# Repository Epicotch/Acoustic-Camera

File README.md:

hi

Firmware is under firmware, actual board is under Microphone board (KiCAD 10), analysis tools is are in pattern analysis, power viewing utility is under power viewer

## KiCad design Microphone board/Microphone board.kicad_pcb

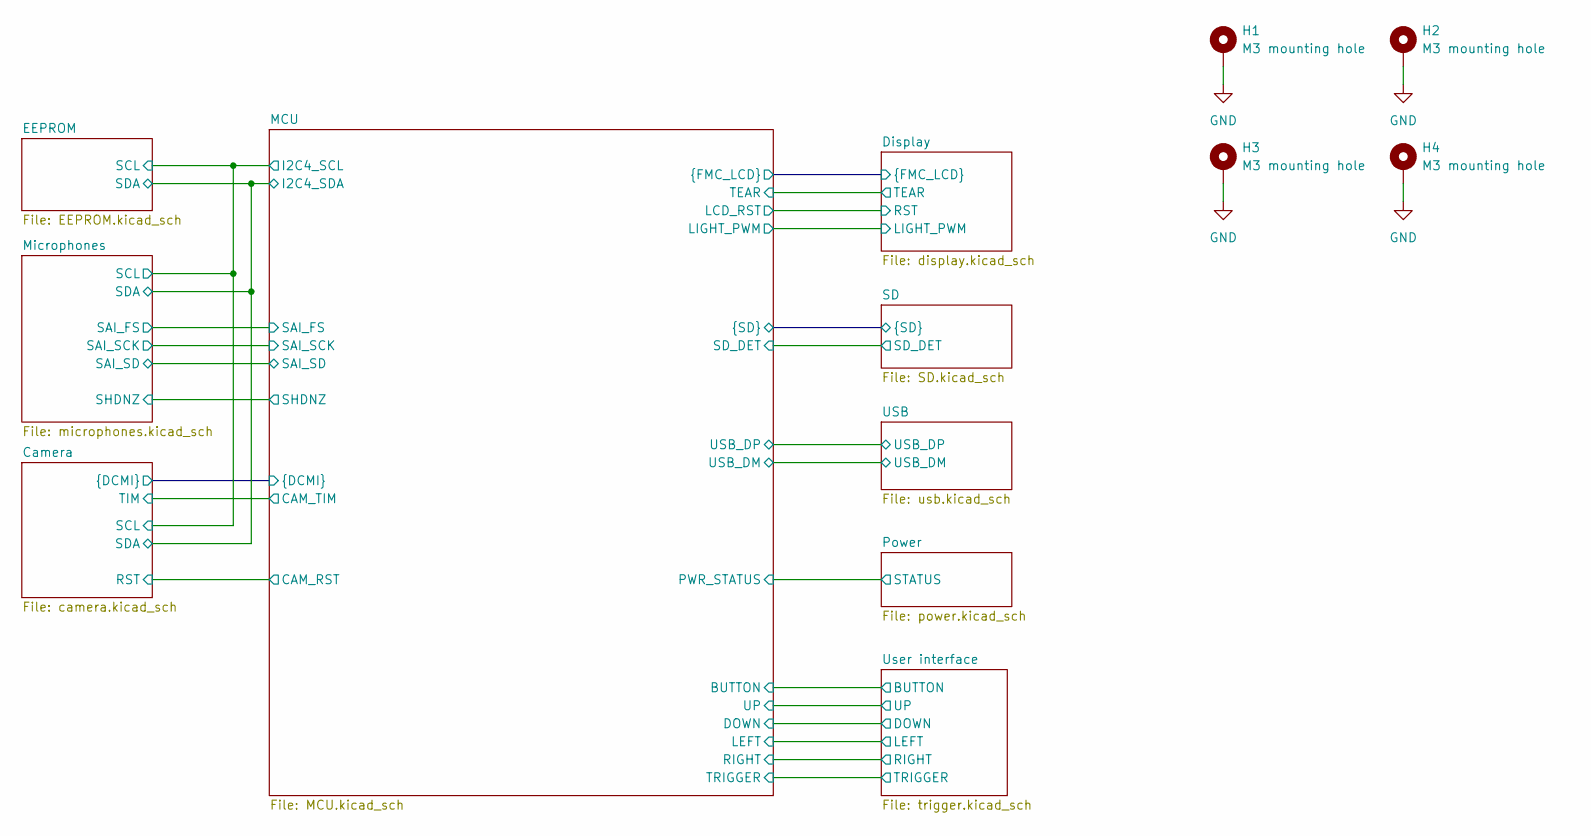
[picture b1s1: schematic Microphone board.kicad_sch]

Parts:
H1, H2, H3, H4: M3 mounting hole; MountingHole_3.2mm_M3_DIN965_Pad

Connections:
GND: H1.1 (1_1), H2.1 (1_1), H3.1 (1_1), H4.1 (1_1); also elsewhere on the board

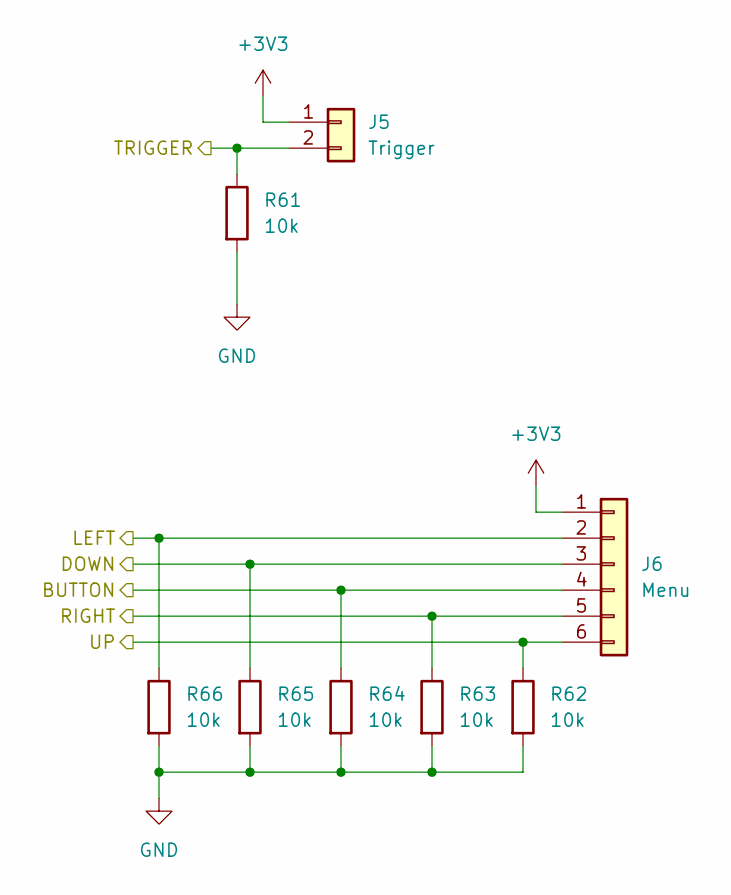
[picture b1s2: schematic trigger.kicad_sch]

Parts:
J5: Trigger; JST_PH_B2B-PH-K_1x02_P2.00mm_Vertical
J6: Menu; JST_PH_B6B-PH-K_1x06_P2.00mm_Vertical
R61, R62, R63, R64, R65, R66: 10k; R_0402_1005Metric

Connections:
+3V3: J5.1, J6.1; also elsewhere on the board
/MCU/BUTTON: J6.4, R64.1; also elsewhere on the board
/MCU/DOWN: J6.3, R65.1; also elsewhere on the board
/MCU/LEFT: J6.2, R66.1; also elsewhere on the board
/MCU/RIGHT: J6.5, R63.1; also elsewhere on the board
/MCU/TRIGGER: J5.2, R61.1; also elsewhere on the board
/MCU/UP: J6.6, R62.1; also elsewhere on the board
GND: R61.2, R62.2, R63.2, R64.2, R65.2, R66.2; also elsewhere on the board

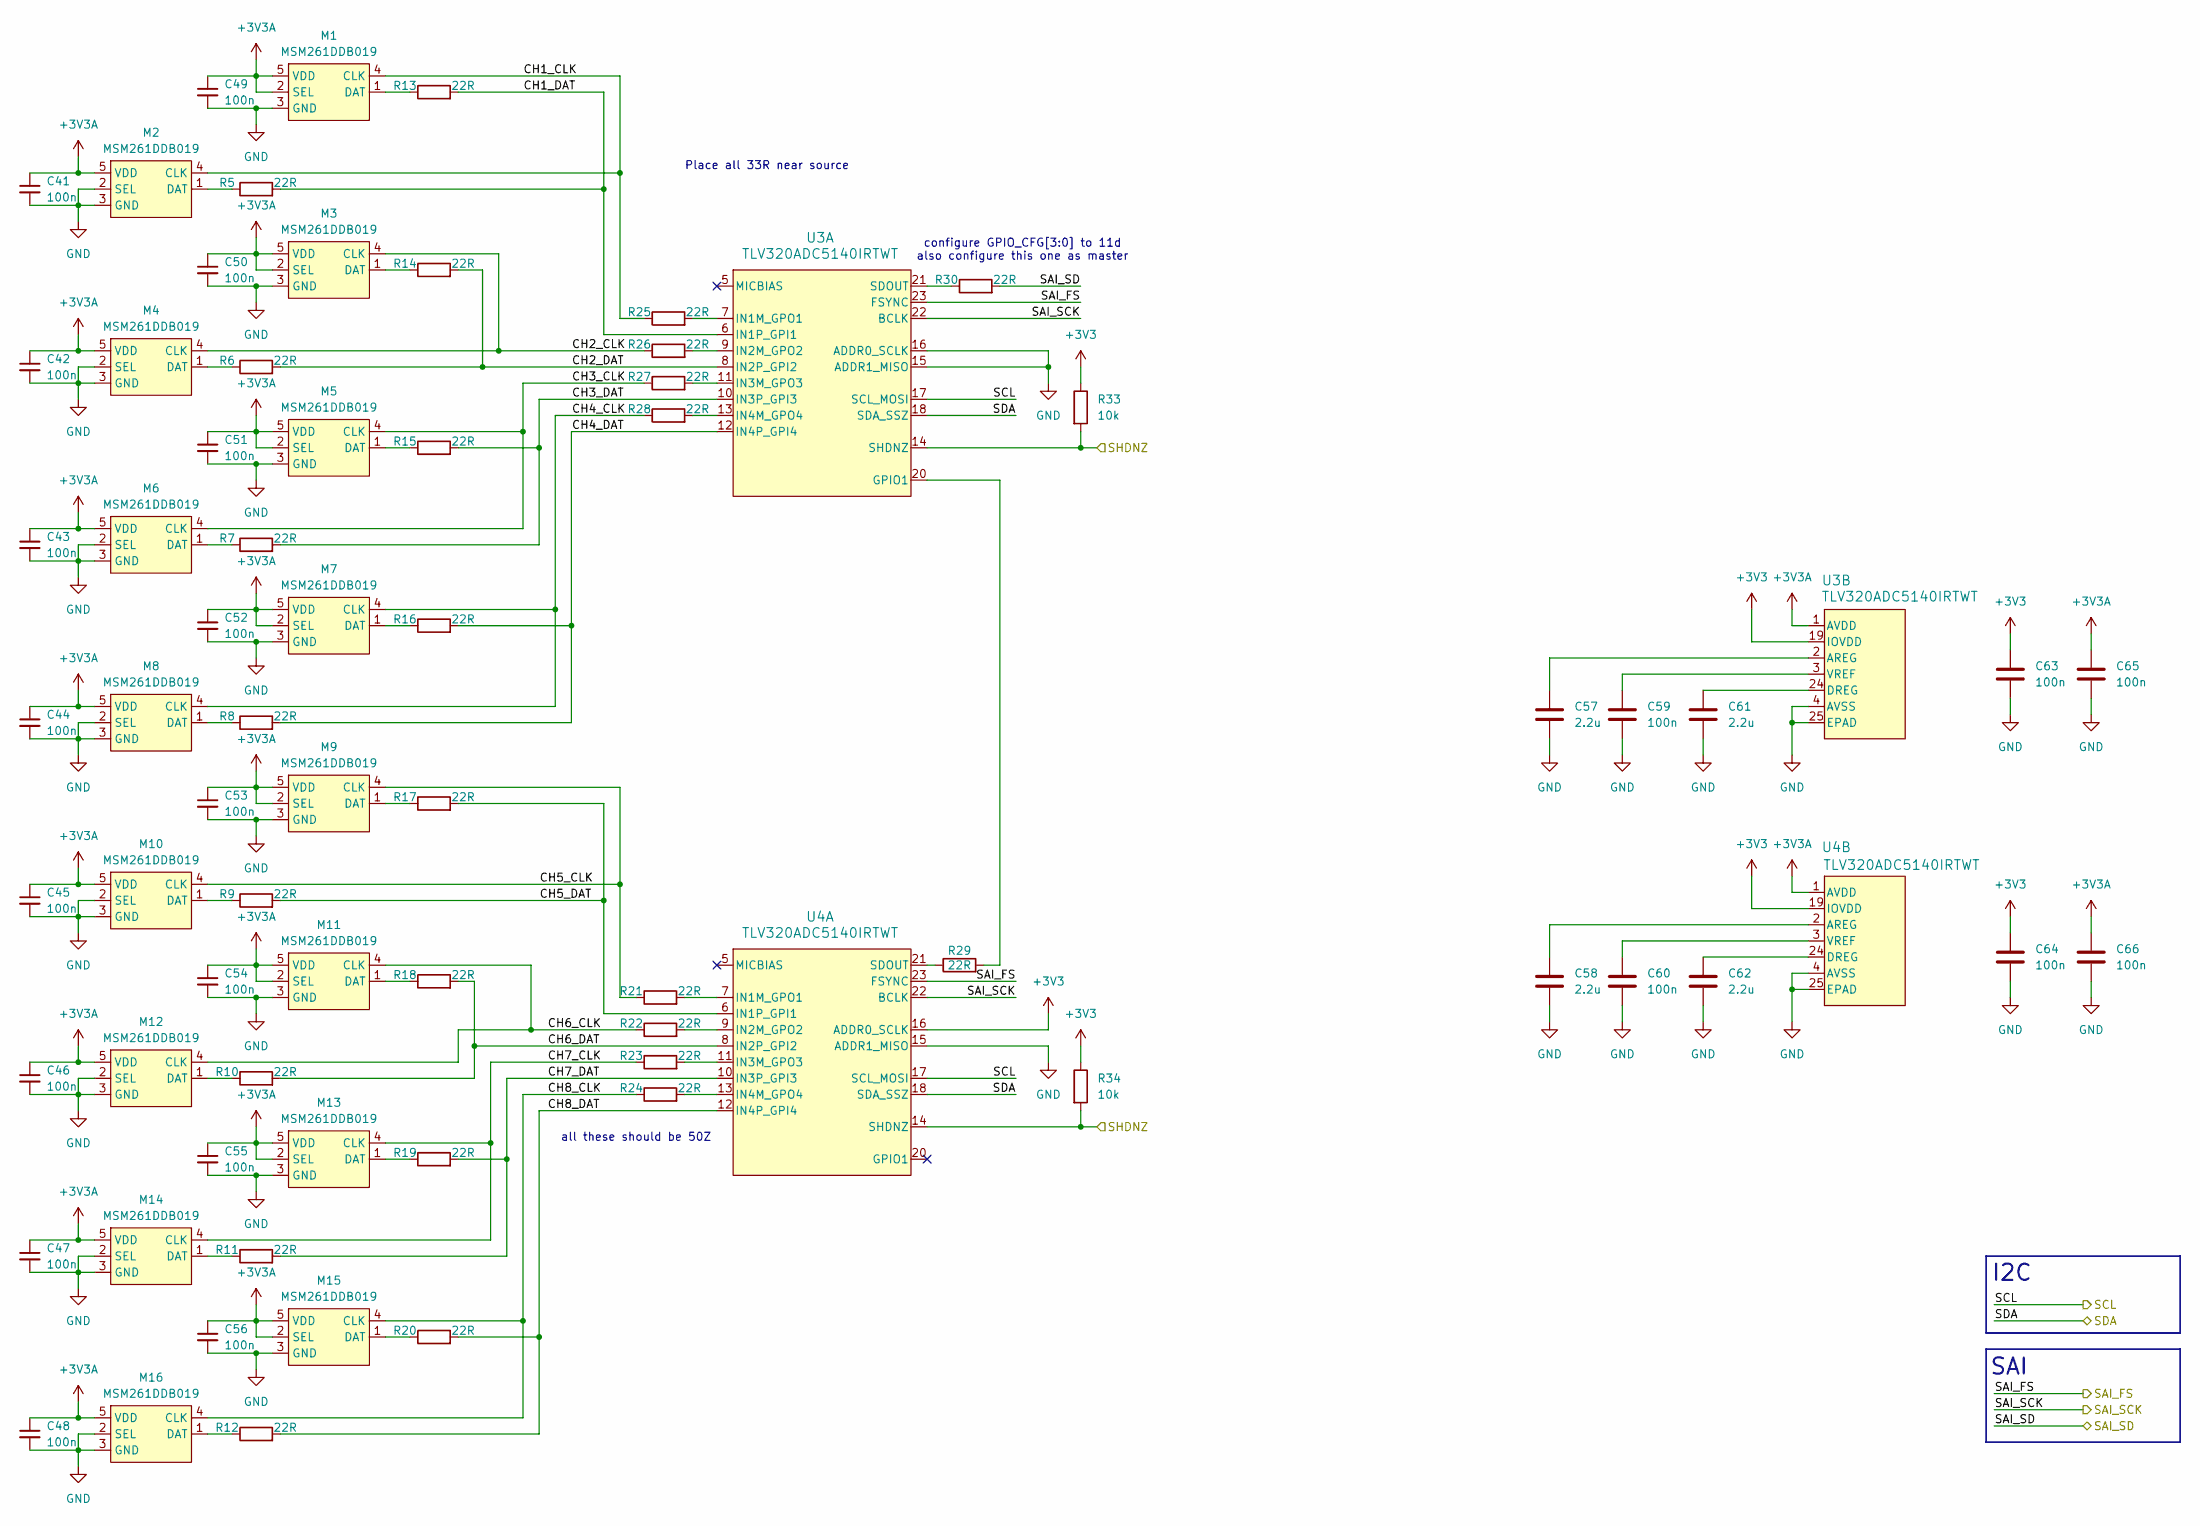
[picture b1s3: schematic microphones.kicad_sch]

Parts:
C41, C42, C43, C44, C45, C46, C47, C48, C49, C50, C51, C52, C53, C54, C55, C56, C59, C60, C63, C64, C65, C66: 100n; C_0402_1005Metric
C57, C58, C61, C62: 2.2u; C_0402_1005Metric
M1, M2, M3, M4, M5, M6, M7, M8, M9, M10, M11, M12, M13, M14, M15, M16: MSM261DDB019
R5, R6, R7, R8, R9, R10, R11, R12, R13, R14, R15, R16, R17, R18, R19, R20, R21, R22, R23, R24, R25, R26, R27, R28, R29, R30: 22R; R_0402_1005Metric
R33, R34: 10k; R_0402_1005Metric
U3, U4: TLV320ADC5140IRTWT; RTW24_4P15X4P15_TEX

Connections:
+3V3: C63.1, C64.1, R33.1, R34.1, U3.19 (IOVDD), U4.16 (ADDR0_SCLK), U4.19 (IOVDD); also elsewhere on the board
+3V3A: C41.1, C42.1, C43.1, C44.1, C45.1, C46.1, C47.1, C48.1, C49.1, C50.1, C51.1, C52.1, C53.1, C54.1, C55.1, C56.1, C65.1, C66.1, M1.2 (SEL), M1.5 (VDD), M2.5 (VDD), M3.2 (SEL), M3.5 (VDD), M4.5 (VDD), M5.2 (SEL), M5.5 (VDD), M6.5 (VDD), M7.2 (SEL), M7.5 (VDD), M8.5 (VDD), M9.2 (SEL), M9.5 (VDD), M10.5 (VDD), M11.2 (SEL), M11.5 (VDD), M12.5 (VDD), M13.2 (SEL), M13.5 (VDD), M14.5 (VDD), M15.2 (SEL), M15.5 (VDD), M16.5 (VDD), U3.1 (AVDD), U4.1 (AVDD); also elsewhere on the board
/MCU/I2C4_SCL: U3.17 (SCL_MOSI), U4.17 (SCL_MOSI); also elsewhere on the board
/MCU/I2C4_SDA: U3.18 (SDA_SSZ), U4.18 (SDA_SSZ); also elsewhere on the board
/MCU/SAI_FS: U3.23 (FSYNC), U4.23 (FSYNC); also elsewhere on the board
/MCU/SAI_SCK: U3.22 (BCLK), U4.22 (BCLK); also elsewhere on the board
/MCU/SAI_SD: R30.2; also elsewhere on the board
/MCU/SHDNZ: R33.2, R34.2, U3.14 (SHDNZ), U4.14 (SHDNZ); also elsewhere on the board
/Microphones/CH1_CLK: M1.4 (CLK), M2.4 (CLK), R25.1
/Microphones/CH1_DAT: R5.2, R13.2, U3.6 (IN1P_GPI1)
/Microphones/CH2_CLK: M3.4 (CLK), M4.4 (CLK), R26.1
/Microphones/CH2_DAT: R6.2, R14.2, U3.8 (IN2P_GPI2)
/Microphones/CH3_CLK: M5.4 (CLK), M6.4 (CLK), R27.1
/Microphones/CH3_DAT: R7.2, R15.2, U3.10 (IN3P_GPI3)
/Microphones/CH4_CLK: M7.4 (CLK), M8.4 (CLK), R28.1
/Microphones/CH4_DAT: R8.2, R16.2, U3.12 (IN4P_GPI4)
/Microphones/CH5_CLK: M9.4 (CLK), M10.4 (CLK), R21.1
/Microphones/CH5_DAT: R9.2, R17.2, U4.6 (IN1P_GPI1)
/Microphones/CH6_CLK: M11.4 (CLK), M12.4 (CLK), R22.1
/Microphones/CH6_DAT: R10.2, R18.2, U4.8 (IN2P_GPI2)
/Microphones/CH7_CLK: M13.4 (CLK), M14.4 (CLK), R23.1
/Microphones/CH7_DAT: R11.2, R19.2, U4.10 (IN3P_GPI3)
/Microphones/CH8_CLK: M15.4 (CLK), M16.4 (CLK), R24.1
/Microphones/CH8_DAT: R12.2, R20.2, U4.12 (IN4P_GPI4)
GND: C41.2, C42.2, C43.2, C44.2, C45.2, C46.2, C47.2, C48.2, C49.2, C50.2, C51.2, C52.2, C53.2, C54.2, C55.2, C56.2, C57.2, C58.2, C59.2, C60.2, C61.2, C62.2, C63.2, C64.2, C65.2, C66.2, M1.3 (GND), M2.2 (SEL), M2.3 (GND), M3.3 (GND), M4.2 (SEL), M4.3 (GND), M5.3 (GND), M6.2 (SEL), M6.3 (GND), M7.3 (GND), M8.2 (SEL), M8.3 (GND), M9.3 (GND), M10.2 (SEL), M10.3 (GND), M11.3 (GND), M12.2 (SEL), M12.3 (GND), M13.3 (GND), M14.2 (SEL), M14.3 (GND), M15.3 (GND), M16.2 (SEL), M16.3 (GND), U3.4 (AVSS), U3.15 (ADDR1_MISO), U3.16 (ADDR0_SCLK), U3.25 (EPAD), U4.4 (AVSS), U4.15 (ADDR1_MISO), U4.25 (EPAD); also elsewhere on the board
unnamed: M1.1 (DAT), R13.1
unnamed: M2.1 (DAT), R5.1
unnamed: M3.1 (DAT), R14.1
unnamed: M4.1 (DAT), R6.1
unnamed: M5.1 (DAT), R15.1
unnamed: M6.1 (DAT), R7.1
unnamed: M7.1 (DAT), R16.1
unnamed: M8.1 (DAT), R8.1
unnamed: M9.1 (DAT), R17.1
unnamed: M10.1 (DAT), R9.1
unnamed: M11.1 (DAT), R18.1
unnamed: M12.1 (DAT), R10.1
unnamed: M13.1 (DAT), R19.1
unnamed: M14.1 (DAT), R11.1
unnamed: M15.1 (DAT), R20.1
unnamed: M16.1 (DAT), R12.1
unnamed: R29.2, U3.20 (GPIO1)
unnamed: R25.2, U3.7 (IN1M_GPO1)
unnamed: R26.2, U3.9 (IN2M_GPO2)
unnamed: R27.2, U3.11 (IN3M_GPO3)
unnamed: R28.2, U3.13 (IN4M_GPO4)
unnamed: R30.1, U3.21 (SDOUT)
unnamed: C57.1, U3.2 (AREG)
unnamed: C61.1, U3.24 (DREG)
unnamed: C59.1, U3.3 (VREF)
unnamed: R21.2, U4.7 (IN1M_GPO1)
unnamed: R22.2, U4.9 (IN2M_GPO2)
unnamed: R23.2, U4.11 (IN3M_GPO3)
unnamed: R24.2, U4.13 (IN4M_GPO4)
unnamed: R29.1, U4.21 (SDOUT)
unnamed: C58.1, U4.2 (AREG)
unnamed: C62.1, U4.24 (DREG)
unnamed: C60.1, U4.3 (VREF)

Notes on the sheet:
SAI
Place all 33R near source
configure GPIO_CFG[3:0] to 11d also configure this one as master
I2C
all these should be 50Z

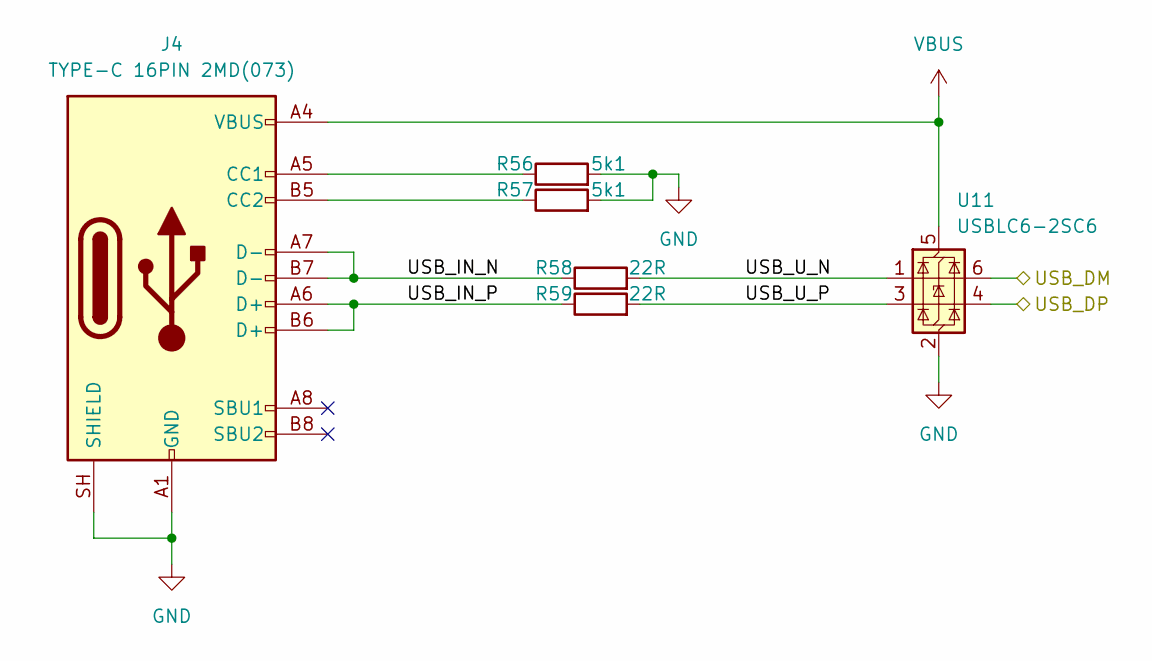
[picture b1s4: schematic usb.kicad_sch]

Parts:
J4: TYPE-C 16PIN 2MD(073); USB_C_Receptacle_HRO_TYPE-C-31-M-12
R56, R57: 5k1; R_0402_1005Metric
R58, R59: 22R; R_0402_1005Metric
U11: USBLC6-2SC6; SOT-23-6

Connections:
/MCU/USB_N: U11.6 (I/O1); also elsewhere on the board
/MCU/USB_P: U11.4 (I/O2); also elsewhere on the board
/USB/USB_IN_N: J4.A7 (D-), J4.B7 (D-), R58.1
/USB/USB_IN_P: J4.A6 (D+), J4.B6 (D+), R59.1
/USB/USB_U_N: R58.2, U11.1 (I/O1)
/USB/USB_U_P: R59.2, U11.3 (I/O2)
GND: J4.A1 (GND), J4.A12 (GND), J4.B1 (GND), J4.B12 (GND), J4.SH (SHIELD), R56.2, R57.2, U11.2 (GND); also elsewhere on the board
unnamed: J4.A5 (CC1), R56.1
unnamed: J4.B5 (CC2), R57.1
VBUS: J4.A4 (VBUS), J4.A9 (VBUS), J4.B4 (VBUS), J4.B9 (VBUS), U11.5 (VBUS); also elsewhere on the board

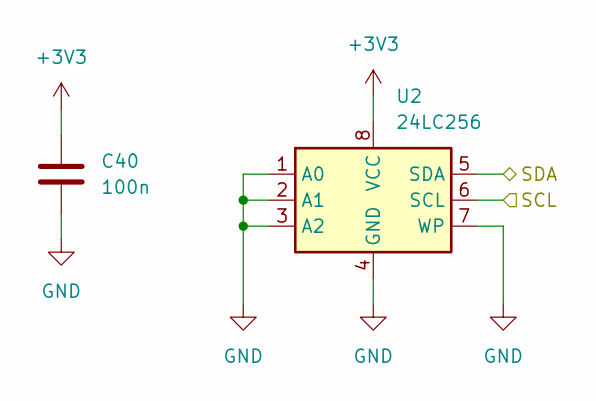
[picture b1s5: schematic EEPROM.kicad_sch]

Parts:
C40: 100n; C_0402_1005Metric
U2: 24LC256; SOIC-8_3.9x4.9mm_P1.27mm

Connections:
+3V3: C40.1, U2.8 (VCC); also elsewhere on the board
/MCU/I2C4_SCL: U2.6 (SCL); also elsewhere on the board
/MCU/I2C4_SDA: U2.5 (SDA); also elsewhere on the board
GND: C40.2, U2.1 (A0), U2.2 (A1), U2.3 (A2), U2.4 (GND), U2.7 (WP); also elsewhere on the board

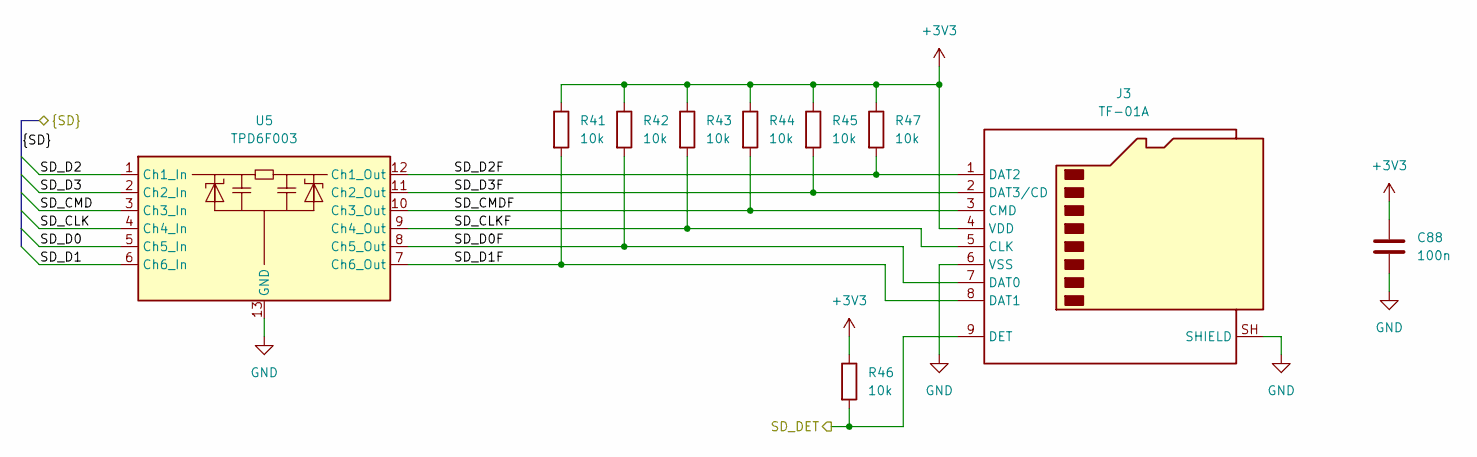
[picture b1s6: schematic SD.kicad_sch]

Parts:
C88: 100n; C_0402_1005Metric
J3: TF-01A
R41, R42, R43, R44, R45, R46, R47: 10k; R_0402_1005Metric
U5: TPD6F003; Texas_R-PWSON-N12_EP0.4x2mm

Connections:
+3V3: C88.1, J3.4 (VDD), R41.1, R42.1, R43.1, R44.1, R45.1, R46.1, R47.1; also elsewhere on the board
/MCU/SD_CLK: U5.4 (Ch4_In); also elsewhere on the board
/MCU/SD_CMD: U5.3 (Ch3_In); also elsewhere on the board
/MCU/SD_D0: U5.5 (Ch5_In); also elsewhere on the board
/MCU/SD_D1: U5.6 (Ch6_In); also elsewhere on the board
/MCU/SD_D2: U5.1 (Ch1_In); also elsewhere on the board
/MCU/SD_D3: U5.2 (Ch2_In); also elsewhere on the board
/MCU/SD_DET: J3.9 (DET), R46.2; also elsewhere on the board
/SD/SD_CLKF: J3.5 (CLK), R43.2, U5.9 (Ch4_Out)
/SD/SD_CMDF: J3.3 (CMD), R44.2, U5.10 (Ch3_Out)
/SD/SD_D0F: J3.7 (DAT0), R42.2, U5.8 (Ch5_Out)
/SD/SD_D1F: J3.8 (DAT1), R41.2, U5.7 (Ch6_Out)
/SD/SD_D2F: J3.1 (DAT2), R47.2, U5.12 (Ch1_Out)
/SD/SD_D3F: J3.2 (DAT3/CD), R45.2, U5.11 (Ch2_Out)
GND: C88.2, J3.6 (VSS), J3.SH (SHIELD), U5.13 (GND); also elsewhere on the board

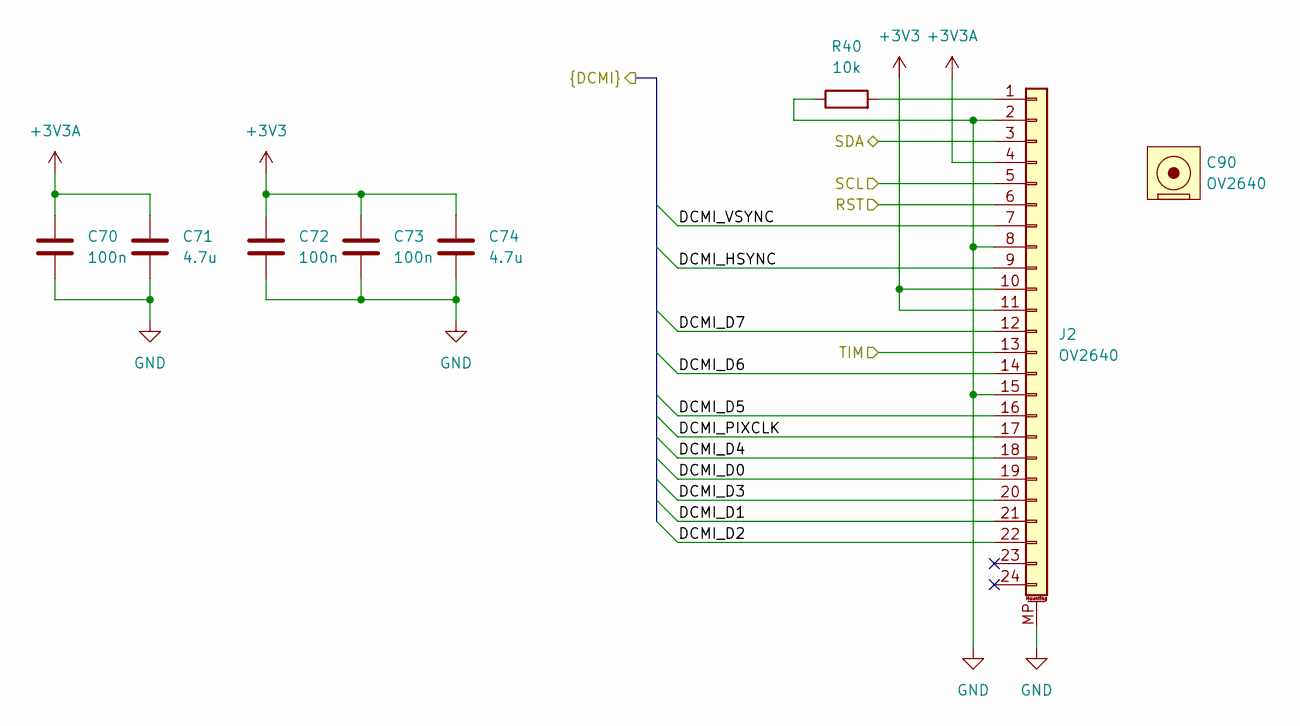
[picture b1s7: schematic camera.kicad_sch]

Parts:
C70, C72, C73: 100n; C_0402_1005Metric
C71, C74: 4.7u; C_0603_1608Metric
C90: OV2640
J2: OV2640; Hirose_FH12-24S-0.5SH_1x24-1MP_P0.50mm_Horizontal
R40: 10k; R_0402_1005Metric

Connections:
+3V3: C72.1, C73.1, C74.1, J2.10, J2.11; also elsewhere on the board
+3V3A: C70.1, C71.1, J2.4; also elsewhere on the board
/MCU/CAM_RST: J2.6; also elsewhere on the board
/MCU/CAM_TIM: J2.13; also elsewhere on the board
/MCU/DCMI_D0: J2.19; also elsewhere on the board
/MCU/DCMI_D1: J2.21; also elsewhere on the board
/MCU/DCMI_D2: J2.22; also elsewhere on the board
/MCU/DCMI_D3: J2.20; also elsewhere on the board
/MCU/DCMI_D4: J2.18; also elsewhere on the board
/MCU/DCMI_D5: J2.16; also elsewhere on the board
/MCU/DCMI_D6: J2.14; also elsewhere on the board
/MCU/DCMI_D7: J2.12; also elsewhere on the board
/MCU/DCMI_HSYNC: J2.9; also elsewhere on the board
/MCU/DCMI_PIXCLK: J2.17; also elsewhere on the board
/MCU/DCMI_VSYNC: J2.7; also elsewhere on the board
/MCU/I2C4_SCL: J2.5; also elsewhere on the board
/MCU/I2C4_SDA: J2.3; also elsewhere on the board
GND: C70.2, C71.2, C72.2, C73.2, C74.2, J2.2, J2.8, J2.15, J2.MP (MountPin), R40.1; also elsewhere on the board
unnamed: J2.1, R40.2

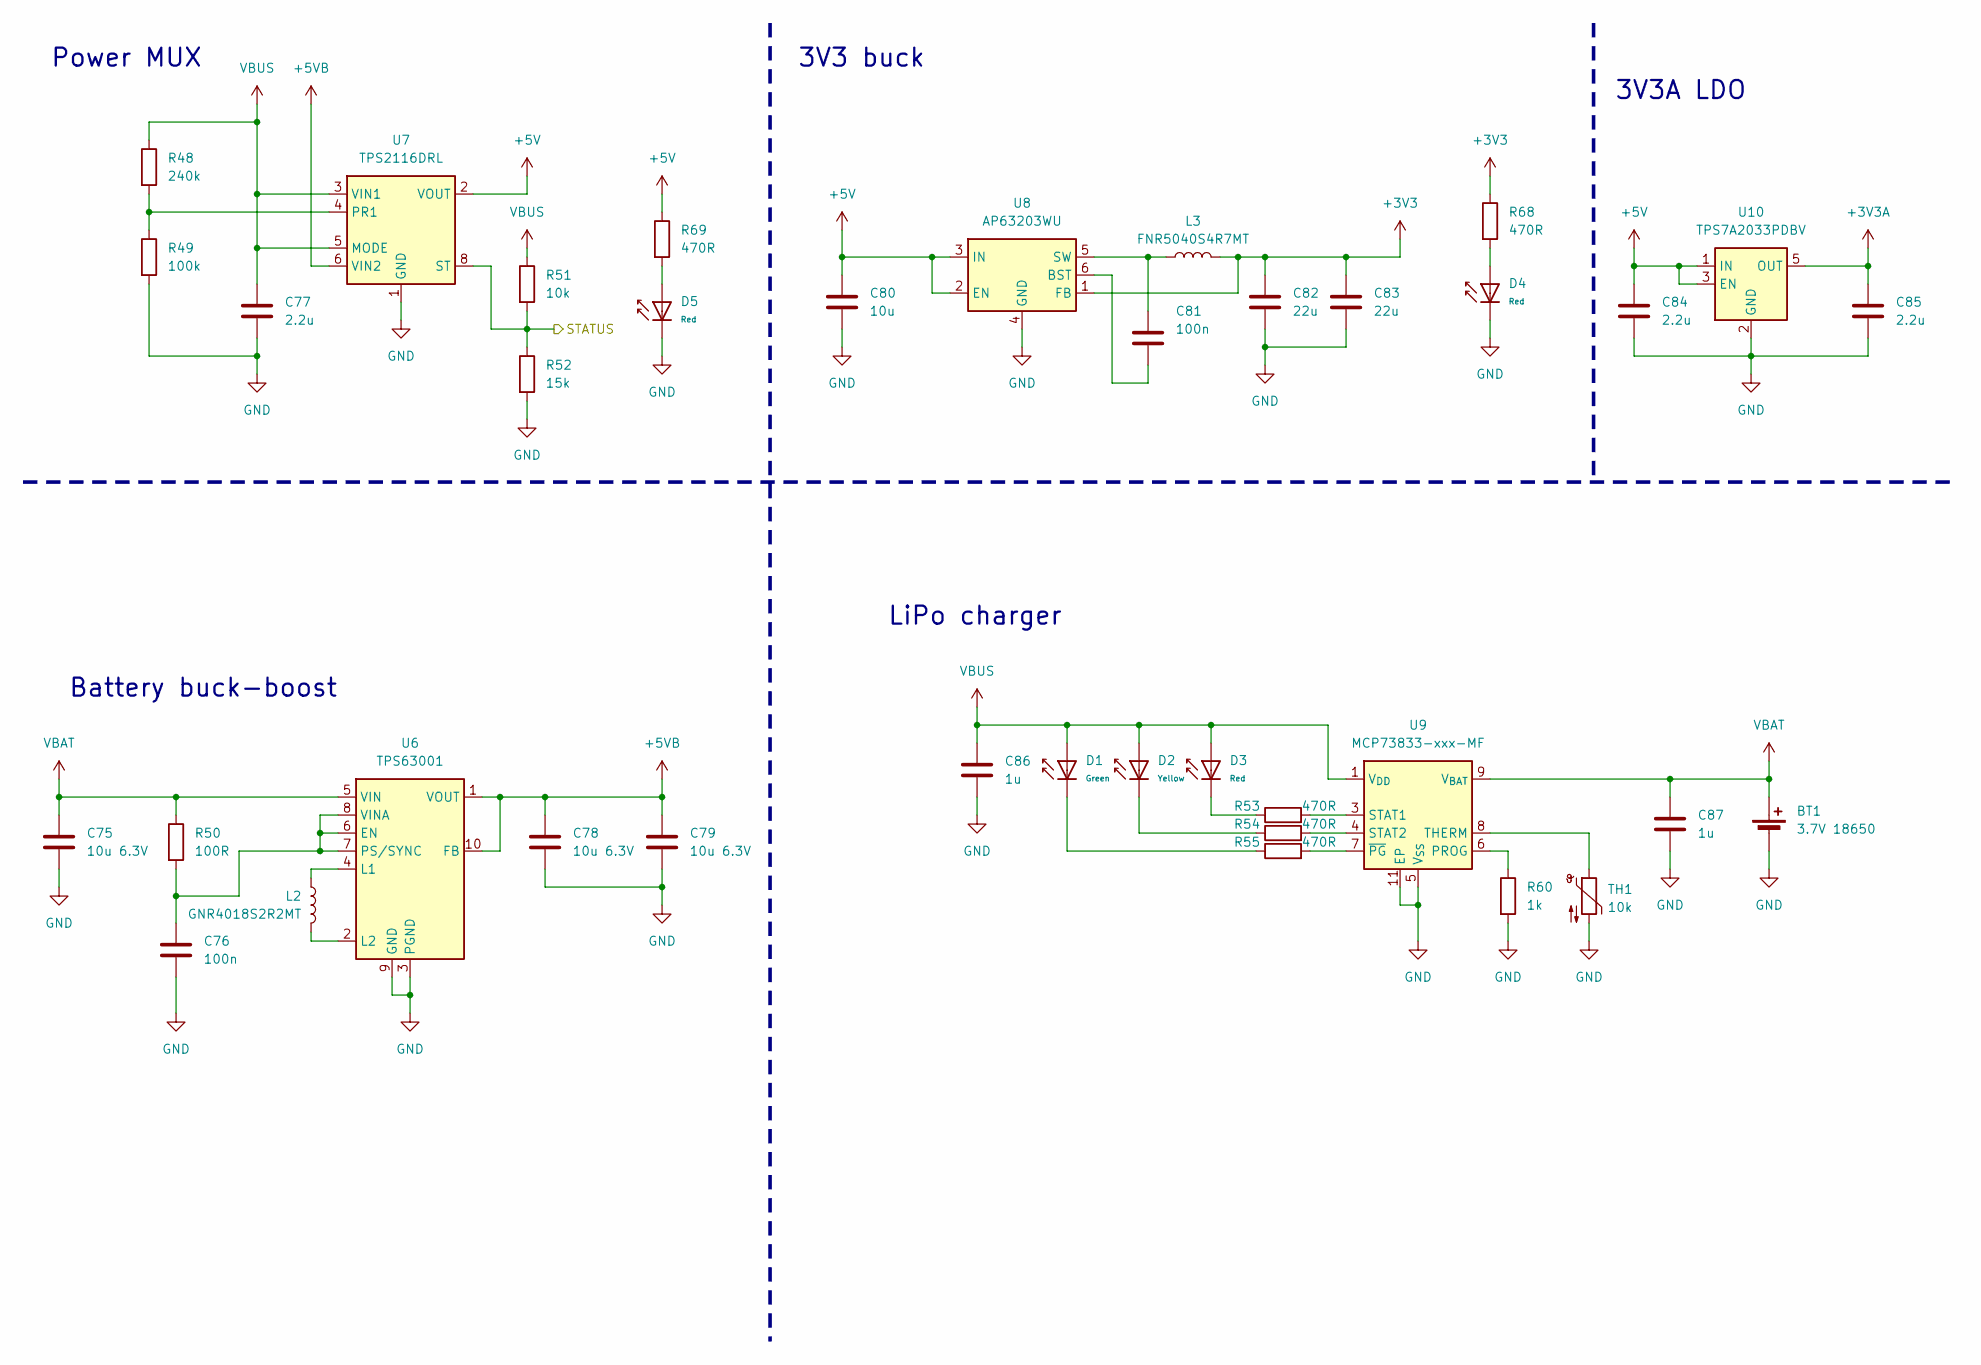
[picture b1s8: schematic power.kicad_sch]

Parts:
BT1: 3.7V 18650; SolderWire-1.5sqmm_1x02_P6mm_D1.7mm_OD3mm
C75, C78, C79: 10u 6.3V; C_0805_2012Metric
C76, C81: 100n; C_0402_1005Metric
C77: 2.2u; C_0402_1005Metric
C80: 10u; C_0603_1608Metric
C82, C83: 22u; C_0805_2012Metric
C84, C85: 2.2u; C_0603_1608Metric
C86, C87: 1u; C_0603_1608Metric
D1: Green; D_0603; Forward Voltage (VF) 1.6V~2.6V; Part NCD0603Y2; LCSC C89811
D2: Yellow; D_0603; Forward Voltage (VF) 1.6V~2.6V; Part NCD0603Y2; LCSC C89811
D3, D4, D5: Red; D_0603; Part KT-0603R; LCSC C2286
L2: GNR4018S2R2MT; L_Abracon_ASPI-4030S
L3: FNR5040S4R7MT; L_Changjiang_FNR5040S
R48: 240k; R_0402_1005Metric
R49: 100k; R_0402_1005Metric
R50: 100R; R_0402_1005Metric
R51: 10k; R_0402_1005Metric
R52: 15k; R_0402_1005Metric
R53, R54, R55, R68, R69: 470R; R_0402_1005Metric
R60: 1k; R_0402_1005Metric
TH1: 10k; JST_PH_B2B-PH-K_1x02_P2.00mm_Vertical
U6: TPS63001; Texas_DRC0010J_ThermalVias
U7: TPS2116DRL; SOT-583-8
U8: AP63203WU; TSOT-23-6
U9: MCP73833-xxx-MF; DFN-10-1EP_3x3mm_P0.5mm_EP1.58x2.35mm
U10: TPS7A2033PDBV; SOT-23-5

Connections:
+3V3: C82.1, C83.1, L3.2, R68.1, U8.1 (FB); also elsewhere on the board
+3V3A: C85.1, U10.5 (OUT); also elsewhere on the board
+5V: C80.1, C84.1, R69.1, U7.2 (VOUT), U7.7 (VOUT), U8.2 (EN), U8.3 (IN), U10.1 (IN), U10.3 (EN)
+5VB: C78.1, C79.1, U6.1 (VOUT), U6.10 (FB), U7.6 (VIN2)
/MCU/PWR_STATUS: R51.2, R52.1, U7.8 (ST); also elsewhere on the board
GND: BT1.2 (-), C75.2, C76.2, C77.2, C78.2, C79.2, C80.2, C82.2, C83.2, C84.2, C85.2, C86.2, C87.2, D4.1, D5.1, R49.2, R52.2, R60.2, TH1.2, U6.3 (PGND), U6.9 (GND), U6.11 (PGND), U7.1 (GND), U8.4 (GND), U9.5 (V_{SS}), U9.11 (EP), U10.2 (GND); also elsewhere on the board
unnamed: D1.1, R55.1
unnamed: D2.1, R54.1
unnamed: D3.1, R53.1
unnamed: D4.2, R68.2
unnamed: D5.2, R69.2
unnamed: C76.1, R50.2, U6.6 (EN), U6.7 (PS/SYNC), U6.8 (VINA)
unnamed: L2.2, U6.4 (L1)
unnamed: L2.1, U6.2 (L2)
unnamed: R48.2, R49.1, U7.4 (PR1)
unnamed: C81.2, U8.6 (BST)
unnamed: C81.1, L3.1, U8.5 (SW)
unnamed: R60.1, U9.6 (PROG)
unnamed: R53.2, U9.3 (STAT1)
unnamed: R54.2, U9.4 (STAT2)
unnamed: TH1.1, U9.8 (THERM)
unnamed: R55.2, U9.7 (~PG)
VBAT: BT1.1 (+), C75.1, C87.1, R50.1, U6.5 (VIN), U9.9 (V_{BAT}), U9.10 (V_{BAT})
VBUS: C77.1, C86.1, D1.2, D2.2, D3.2, R48.1, R51.1, U7.3 (VIN1), U7.5 (MODE), U9.1 (V_{DD}), U9.2 (V_{DD}); also elsewhere on the board

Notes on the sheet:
3V3 buck
3V3A LDO
LiPo charger
Battery buck-boost
Power MUX

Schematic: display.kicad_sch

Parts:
C67, C68: 100n; C_0402_1005Metric
C69: 4.7u; C_0603_1608Metric
J1: NHD-2.4-240320AF-CSXP; Hirose_FH12-40S-0.5SH_1x40-1MP_P0.50mm_Horizontal
Q1: MMBT3904; SOT-23
Q2: AO3401A; SOT-23
R35: 1k; R_0402_1005Metric
R36: 10k; R_0402_1005Metric
R37: 4k7; R_0402_1005Metric
R38: 10R; R_0402_1005Metric
R39: 2R; R_0603_1608Metric

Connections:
+3V3: C67.1, C68.1, C69.1, J1.33, J1.34, Q2.2 (S), R37.2; also elsewhere on the board
/Display/LIGHT: J1.3, R39.2
/MCU/FMC_D0: J1.27; also elsewhere on the board
/MCU/FMC_D1: J1.26; also elsewhere on the board
/MCU/FMC_D2: J1.25; also elsewhere on the board
/MCU/FMC_D3: J1.24; also elsewhere on the board
/MCU/FMC_D4: J1.23; also elsewhere on the board
/MCU/FMC_D5: J1.22; also elsewhere on the board
/MCU/FMC_D6: J1.21; also elsewhere on the board
/MCU/FMC_D7: J1.20; also elsewhere on the board
/MCU/FMC_D8: J1.19; also elsewhere on the board
/MCU/FMC_D9: J1.18; also elsewhere on the board
/MCU/FMC_D10: J1.17; also elsewhere on the board
/MCU/FMC_D11: J1.16; also elsewhere on the board
/MCU/FMC_D12: J1.15; also elsewhere on the board
/MCU/FMC_D13: J1.14; also elsewhere on the board
/MCU/FMC_D14: J1.13; also elsewhere on the board
/MCU/FMC_D15: J1.12; also elsewhere on the board
/MCU/FMC_NE1: J1.31; also elsewhere on the board
/MCU/FMC_NOE: J1.28; also elsewhere on the board
/MCU/FMC_NWE: J1.29; also elsewhere on the board
/MCU/FMC_RS: J1.30; also elsewhere on the board
/MCU/LCD_RST: J1.11; also elsewhere on the board
/MCU/LIGHT_PWM: R35.1; also elsewhere on the board
/MCU/TEAR: J1.1; also elsewhere on the board
GND: C67.2, C68.2, C69.2, J1.2, J1.4, J1.5, J1.6, J1.7, J1.8, J1.9, J1.10, J1.32, J1.40, J1.MP (MountPin), Q1.2 (E), R36.1; also elsewhere on the board
unnamed: Q1.1 (B), R35.2, R36.2
unnamed: Q1.3 (C), R37.1, R38.1
unnamed: Q2.3 (D), R39.1
unnamed: Q2.1 (G), R38.2

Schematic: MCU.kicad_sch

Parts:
C1: 220pF; C_0402_1005Metric
C2, C3, C5: 2.2u; C_0603_1608Metric
C4, C37: 4.7u; C_0603_1608Metric
C6, C7: 10u; C_0805_2012Metric
C8, C9, C10, C11, C12, C13, C14, C16, C17, C18, C19, C20, C21, C22, C23, C24, C25, C26, C27, C28, C29, C30, C31, C32, C33, C34, C35, C36, C89: 100n; C_0201_0603Metric
C15, C38: 1u; C_0603_1608Metric
C39: 100n; C_0402_1005Metric
D6: Red; D_0603; Part KT-0603R; LCSC C2286
J7: Conn_ARM_JTAG_SWD_10; PinHeader_2x05_P1.27mm_Vertical_SMD
L1: GNR4018S2R2MT; L_Abracon_ASPI-4030S
R1, R4: 10k; R_0402_1005Metric
R2, R3: 2k2; R_0402_1005Metric
R67: 22R; R_0402_1005Metric
R70: 470R; R_0402_1005Metric
S1, S2: Tactile Button, 160gf; SW_TS-1088-AR02016; Voltage Rating (Dc) 12V; Part TS-1088-AR02016; LCSC C720477
U1: STM32H747XIH6; TFBGA-265_14x14mm_Layout17x17_P0.8mm
Y1: SX2M25.000M20F30TNN; Oscillator_SMD_Kyocera_KC2520Z-4Pin_2.5x2.0mm

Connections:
+3V3: C6.1, C7.1, C8.1, C9.1, C10.1, C12.1, C13.1, C14.1, C16.1, C17.1, C18.1, C19.1, C20.1, C21.1, C22.1, C23.1, C24.1, C25.1, C26.1, C27.1, C28.1, C29.1, C30.1, C31.1, C32.1, C33.1, C34.1, C35.1, C36.1, C37.1, C38.1, C39.1, C89.1, J7.1 (VTref), L1.2, R1.1, R2.1, R3.1, S2.1 (A), U1.A6 (VDDLDO), U1.B1 (VBAT), U1.C17 (VDDLDO), U1.E6 (VDD), U1.E7 (PDR_ON), U1.E9 (VDD), U1.E11 (VDD), U1.F5 (VDD), U1.F17 (VDD33_USB), U1.G2 (VFBSMPS), U1.G5 (VDD), U1.G13 (VDD), U1.G17 (VDD50_USB), U1.H5 (VDD), U1.H13 (VDD), U1.J13 (VDD), U1.K5 (VDD), U1.K13 (VDD), U1.L5 (VDD), U1.L13 (VDD), U1.M5 (VDD), U1.M13 (VDD), U1.N7 (VDD), U1.N8 (VDD), U1.N10 (VDD), U1.N11 (VDD), U1.N12 (VDD), U1.P17 (VDDDSI), U1.U12 (VDDLDO), Y1.4 (VDD); also elsewhere on the board
+3V3A: C11.1, C15.1, U1.L1 (VDDA), U1.M1 (VREF+); also elsewhere on the board
/MCU/BOOT0: R4.1, S2.2 (B), U1.E8 (BOOT0)
/MCU/BUTTON: U1.U5 (PB0); also elsewhere on the board
/MCU/CAM_RST: U1.B5 (PB6); also elsewhere on the board
/MCU/CAM_TIM: R67.1; also elsewhere on the board
/MCU/DCMI_D0: U1.D15 (PA9); also elsewhere on the board
/MCU/DCMI_D1: U1.D14 (PA10); also elsewhere on the board
/MCU/DCMI_D2: U1.C4 (PE0); also elsewhere on the board
/MCU/DCMI_D3: U1.B4 (PE1); also elsewhere on the board
/MCU/DCMI_D4: U1.B17 (PH14); also elsewhere on the board
/MCU/DCMI_D5: U1.A4 (PI4); also elsewhere on the board
/MCU/DCMI_D6: U1.A2 (PI6); also elsewhere on the board
/MCU/DCMI_D7: U1.B3 (PI7); also elsewhere on the board
/MCU/DCMI_HSYNC: U1.T13 (PH8); also elsewhere on the board
/MCU/DCMI_PIXCLK: U1.R3 (PA6); also elsewhere on the board
/MCU/DCMI_VSYNC: U1.A3 (PI5); also elsewhere on the board
/MCU/DOWN: U1.U4 (PC5); also elsewhere on the board
/MCU/FMC_D0: U1.P16 (PD14); also elsewhere on the board
/MCU/FMC_D1: U1.P15 (PD15); also elsewhere on the board
/MCU/FMC_D2: U1.D13 (PD0); also elsewhere on the board
/MCU/FMC_D3: U1.E12 (PD1); also elsewhere on the board
/MCU/FMC_D4: U1.U9 (PE7); also elsewhere on the board
/MCU/FMC_D5: U1.T9 (PE8); also elsewhere on the board
/MCU/FMC_D6: U1.P9 (PE9); also elsewhere on the board
/MCU/FMC_D7: U1.N9 (PE10); also elsewhere on the board
/MCU/FMC_D8: U1.P10 (PE11); also elsewhere on the board
/MCU/FMC_D9: U1.R10 (PE12); also elsewhere on the board
/MCU/FMC_D10: U1.T10 (PE13); also elsewhere on the board
/MCU/FMC_D11: U1.U10 (PE14); also elsewhere on the board
/MCU/FMC_D12: U1.R11 (PE15); also elsewhere on the board
/MCU/FMC_D13: U1.U16 (PD8); also elsewhere on the board
/MCU/FMC_D14: U1.T17 (PD9); also elsewhere on the board
/MCU/FMC_D15: U1.T16 (PD10); also elsewhere on the board
/MCU/FMC_NE1: U1.C11 (PD7); also elsewhere on the board
/MCU/FMC_NOE: U1.A12 (PD4); also elsewhere on the board
/MCU/FMC_NWE: U1.A11 (PD5); also elsewhere on the board
/MCU/FMC_RS: U1.P7 (PF13); also elsewhere on the board
/MCU/HSE: U1.J2 (OSC_IN), Y1.3 (OUT)
/MCU/I2C4_SCL: R3.2, U1.P8 (PF14); also elsewhere on the board
/MCU/I2C4_SDA: R2.2, U1.R9 (PF15); also elsewhere on the board
/MCU/LCD_RST: U1.T15 (PB15); also elsewhere on the board
/MCU/LEFT: U1.U3 (PA4); also elsewhere on the board
/MCU/LIGHT_PWM: U1.P13 (PH10); also elsewhere on the board
/MCU/NRST: J7.10 (~RESET), R1.2, S1.1 (A), U1.K1 (NRST)
/MCU/PWR_STATUS: U1.H17 (PK2); also elsewhere on the board
/MCU/RIGHT: U1.U6 (PJ3); also elsewhere on the board
/MCU/SAI_FS: U1.D2 (PE4); also elsewhere on the board
/MCU/SAI_SCK: U1.D1 (PE5); also elsewhere on the board
/MCU/SAI_SD: U1.B11 (PD6); also elsewhere on the board
/MCU/SD_CLK: U1.C12; also elsewhere on the board
/MCU/SD_CMD: U1.D12 (PD2); also elsewhere on the board
/MCU/SD_D0: U1.E13 (PC8); also elsewhere on the board
/MCU/SD_D1: U1.E14 (PC9); also elsewhere on the board
/MCU/SD_D2: U1.A13 (PC10); also elsewhere on the board
/MCU/SD_D3: U1.B13 (PC11); also elsewhere on the board
/MCU/SD_DET: U1.A15 (PI1); also elsewhere on the board
/MCU/SHDNZ: U1.B10 (PJ15); also elsewhere on the board
/MCU/STATUS_LED: R70.1, U1.T3 (PA5)
/MCU/SWCLK: J7.4 (SWCLK/TCK), U1.B14 (SWCLK)
/MCU/SWDIO: J7.2 (SWDIO/TMS), U1.C15 (SWDIO)
/MCU/SWO: J7.6 (SWO/TDO), U1.R6 (PB2)
/MCU/TEAR: U1.U15 (PB14); also elsewhere on the board
/MCU/TRIGGER: U1.U2 (PA3); also elsewhere on the board
/MCU/UP: U1.U7 (PJ4); also elsewhere on the board
/MCU/USB_N: U1.E17 (PA11); also elsewhere on the board
/MCU/USB_P: U1.E16 (PA12); also elsewhere on the board
GND: C1.2, C2.2, C3.2, C4.2, C5.2, C6.2, C7.2, C8.2, C9.2, C10.2, C11.2, C12.2, C13.2, C14.2, C15.2, C16.2, C17.2, C18.2, C19.2, C20.2, C21.2, C22.2, C23.2, C24.2, C25.2, C26.2, C27.2, C28.2, C29.2, C30.2, C31.2, C32.2, C33.2, C34.2, C35.2, C36.2, C37.2, C38.2, C39.2, C89.2, D6.1, J7.3 (GND), J7.5 (GND), J7.9 (GNDDetect), R4.2, S1.2 (B), U1.A1 (VSS), U1.A17 (VSS), U1.B2 (VSS), U1.B6 (VSS), U1.C10 (VSS), U1.C13 (VSS), U1.C16 (VSS), U1.F2 (VSSSMPS), U1.G7 (VSS), U1.G8 (VSS), U1.G9 (VSS), U1.G10 (VSS), U1.G11 (VSS), U1.G16 (VSS), U1.H7 (VSS), U1.H8 (VSS), U1.H9 (VSS), U1.H10 (VSS), U1.H11 (VSS), U1.J3 (VSS), U1.J7 (VSS), U1.J8 (VSS), U1.J9 (VSS), U1.J10 (VSS), U1.J11 (VSS), U1.J16 (VSS), U1.J17 (VSS), U1.K7 (VSS), U1.K8 (VSS), U1.K9 (VSS), U1.K10 (VSS), U1.K11 (VSS), U1.K15 (VSSDSI), U1.L7 (VSS), U1.L8 (VSS), U1.L9 (VSS), U1.L10 (VSS), U1.L11 (VSS), U1.N1 (VREF-), U1.N16 (VSS), U1.P1 (VSSA), U1.R4 (VSS), U1.R8 (VSS), U1.T12 (VSS), U1.U1 (VSS), U1.U17 (VSS), Y1.2 (GND); also elsewhere on the board
unnamed: C3.1, C5.1, U1.A7 (VCAP), U1.D17 (VCAP), U1.U11 (VCAP)
unnamed: D6.2, R70.2
unnamed: C2.1, U1.N17 (VCAPDSI)
unnamed: C4.1, U1.F1 (VDDSMPS)
unnamed: C1.1, L1.1, U1.E1 (VLXSMPS)
unnamed: R67.2, U1.A5 (PB5)

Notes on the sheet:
USB
Oscillator
FMC LCD
DCMI
STATUS
SAI
so basically everything should be 50 ohms
TODO: check for any routing particularities (like pullups)
BOOT/NRST Switches
I2C
Power
